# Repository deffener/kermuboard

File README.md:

== Kermuboard ==

- Normal/Stepped CAPS
- O-ring gasket mount
- Splitterino pepperino
- "Handwire" rotary encoder with huge clearance for >40mm knob
- Acrylic case

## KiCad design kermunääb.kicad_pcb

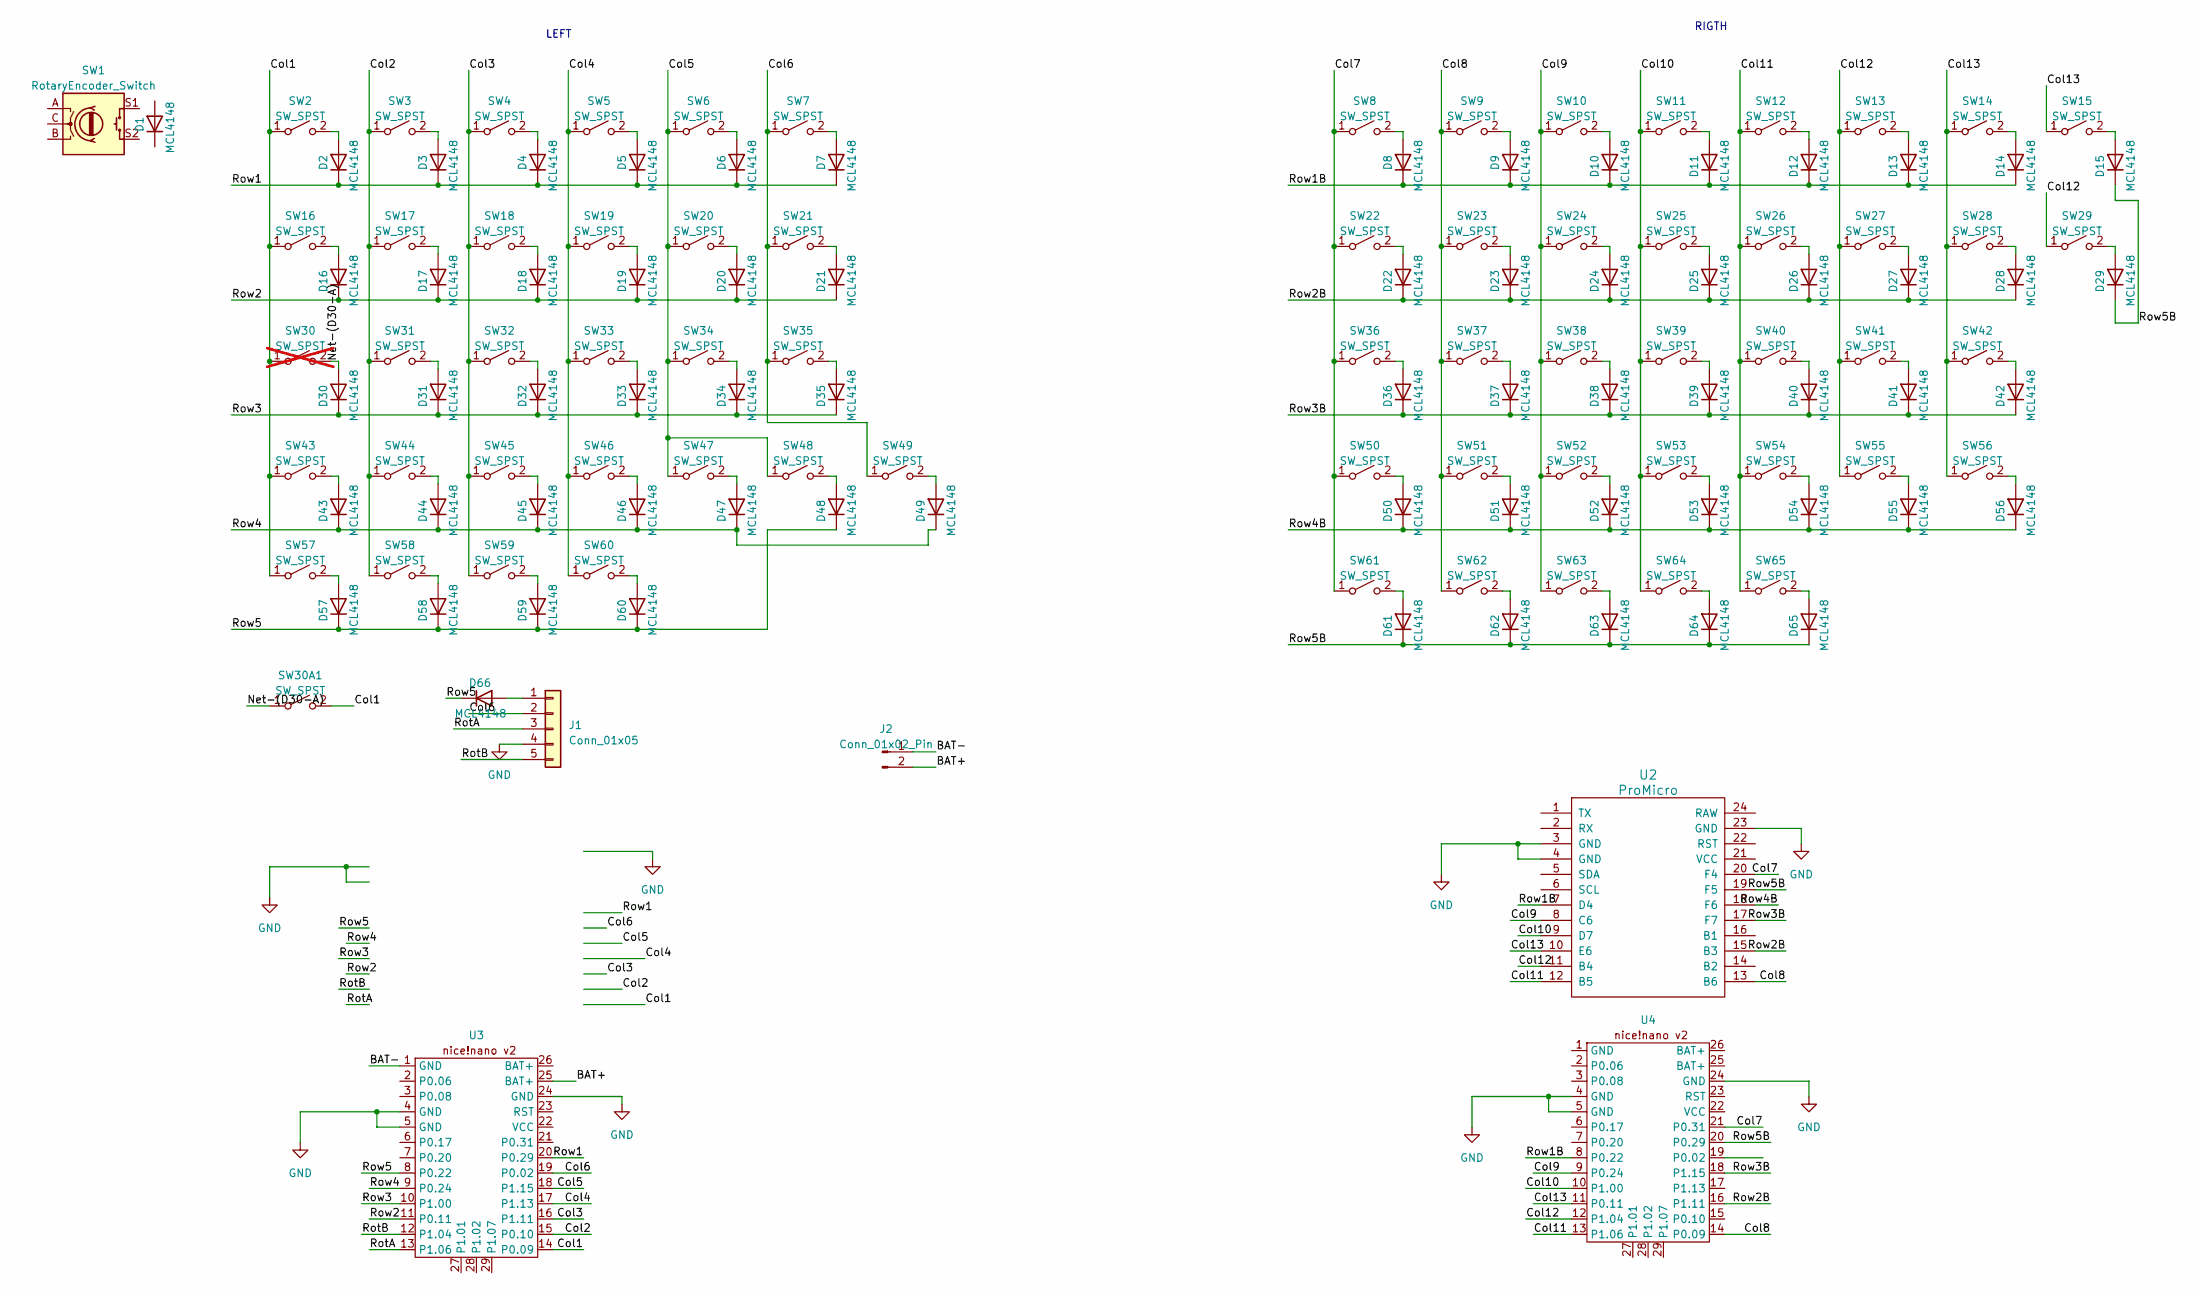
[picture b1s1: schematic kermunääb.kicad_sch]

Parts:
D1, D2, D3, D4, D5, D6, D7, D8, D9, D10, D11, D12, D13, D14, D15, D16, D17, D18, D19, D20, D21, D22, D23, D24, D25, D26, D27, D28, D29, D30, D31, D32, D33, D34, D35, D36, D37, D38, D39, D40, D41, D42, D43, D44, D45, D46, D47, D48, D49, D50, D51, D52, D53, D54, D55, D56, D57, D58, D59, D60, D61, D62, D63, D64, D65, D66: MCL4148; D_MicroMELF
J1: Conn_01x05; PinSocket_1x05_P2.54mm_Horizontal
J2: Conn_01x02_Pin; JST_XH_S2B-XH-A-1_1x02_P2.50mm_Horizontal
SW1: RotaryEncoder_Switch; RotaryEncoder_Alps_EC11E-Switch_Vertical_H20mm
SW2, SW3, SW4, SW5, SW6, SW7, SW8, SW9, SW10, SW11, SW12, SW13, SW14, SW17, SW18, SW19, SW20, SW21, SW22, SW23, SW24, SW25, SW26, SW27, SW28, SW31, SW32, SW33, SW34, SW35, SW36, SW37, SW38, SW39, SW40, SW41, SW42, SW44, SW45, SW46, SW47, SW48, SW49, SW50, SW51, SW52, SW53, SW54, SW55, SW58: SW_SPST; SW_Cherry_MX_PCB_1.00u
SW15: SW_SPST; SW_Cherry_MX_PCB_2.00u
SW16, SW57, SW59: SW_SPST; SW_Cherry_MX_PCB_1.50u
SW29: SW_SPST; SW_Cherry_MX_PCB_ISOEnter
SW30: SW_SPST; SW_Cherry_MX_PCB_1.75u; not fitted
SW30A1: SW_SPST; SW_Cherry_MX_PCB
SW43, SW62, SW63, SW64, SW65: SW_SPST; SW_Cherry_MX_PCB_1.25u
SW56, SW60, SW61: SW_SPST; SW_Cherry_MX_PCB_1.75u
U2: ProMicro
U3, U4: nice_nanov2_noextras

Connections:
/BAT+: J2.2, U3.25 (BAT+)
/BAT-: J2.1, U3.1 (GND)
/Col1: SW2.1 (A), SW16.1 (A), SW30.1 (A), SW30A1.2 (B), SW43.1 (A), SW57.1 (A), U3.14 (P0.09)
/Col2: SW3.1 (A), SW17.1 (A), SW31.1 (A), SW44.1 (A), SW58.1 (A), U3.15 (P0.10)
/Col3: SW4.1 (A), SW18.1 (A), SW32.1 (A), SW45.1 (A), SW59.1 (A), U3.16 (P1.11)
/Col4: SW5.1 (A), SW19.1 (A), SW33.1 (A), SW46.1 (A), SW60.1 (A), U3.17 (P1.13)
/Col5: SW6.1 (A), SW20.1 (A), SW34.1 (A), SW47.1 (A), SW48.1 (A), U3.18 (P1.15)
/Col6: J1.2, SW7.1 (A), SW21.1 (A), SW35.1 (A), SW49.1 (A), U3.19 (P0.02)
/Col7: SW8.1 (A), SW22.1 (A), SW36.1 (A), SW50.1 (A), SW61.1 (A), U2.20 (F4), U4.21 (P0.31)
/Col8: SW9.1 (A), SW23.1 (A), SW37.1 (A), SW51.1 (A), SW62.1 (A), U2.13 (B6), U4.14 (P0.09)
/Col9: SW10.1 (A), SW24.1 (A), SW38.1 (A), SW52.1 (A), SW63.1 (A), U2.8 (C6), U4.9 (P0.24)
/Col10: SW11.1 (A), SW25.1 (A), SW39.1 (A), SW53.1 (A), SW64.1 (A), U2.9 (D7), U4.10 (P1.00)
/Col11: SW12.1 (A), SW26.1 (A), SW40.1 (A), SW54.1 (A), SW65.1 (A), U2.12 (B5), U4.13 (P1.06)
/Col12: SW13.1 (A), SW27.1 (A), SW29.1 (A), SW41.1 (A), SW55.1 (A), U2.11 (B4), U4.12 (P1.04)
/Col13: SW14.1 (A), SW15.1 (A), SW28.1 (A), SW42.1 (A), SW56.1 (A), U2.10 (E6), U4.11 (P0.11)
/Net-(D30-A): D30.2 (A), SW30.2 (B), SW30A1.1 (A)
/RotA: J1.3, U3.13 (P1.06)
/RotB: J1.5, U3.12 (P1.04)
/Row1: D2.1 (K), D3.1 (K), D4.1 (K), D5.1 (K), D6.1 (K), D7.1 (K), U3.20 (P0.29)
/Row1B: D8.1 (K), D9.1 (K), D10.1 (K), D11.1 (K), D12.1 (K), D13.1 (K), D14.1 (K), U2.7 (D4), U4.8 (P0.22)
/Row2: D16.1 (K), D17.1 (K), D18.1 (K), D19.1 (K), D20.1 (K), D21.1 (K), U3.11 (P0.11)
/Row2B: D22.1 (K), D23.1 (K), D24.1 (K), D25.1 (K), D26.1 (K), D27.1 (K), D28.1 (K), U2.15 (B3), U4.16 (P1.11)
/Row3: D30.1 (K), D31.1 (K), D32.1 (K), D33.1 (K), D34.1 (K), D35.1 (K), U3.10 (P1.00)
/Row3B: D36.1 (K), D37.1 (K), D38.1 (K), D39.1 (K), D40.1 (K), D41.1 (K), D42.1 (K), U2.17 (F7), U4.18 (P1.15)
/Row4: D43.1 (K), D44.1 (K), D45.1 (K), D46.1 (K), D47.1 (K), D49.1 (K), U3.9 (P0.24)
/Row4B: D50.1 (K), D51.1 (K), D52.1 (K), D53.1 (K), D54.1 (K), D55.1 (K), D56.1 (K), U2.18 (F6)
/Row5: D48.1 (K), D57.1 (K), D58.1 (K), D59.1 (K), D60.1 (K), D66.1 (K), U3.8 (P0.22)
/Row5B: D15.1 (K), D29.1 (K), D61.1 (K), D62.1 (K), D63.1 (K), D64.1 (K), D65.1 (K), U2.19 (F5), U4.20 (P0.29)
GND: J1.4, U2.3 (GND), U2.4 (GND), U2.23 (GND), U3.4 (GND), U3.5 (GND), U3.24 (GND), U4.4 (GND), U4.5 (GND), U4.24 (GND)
unnamed: D2.2 (A), SW2.2 (B)
unnamed: D3.2 (A), SW3.2 (B)
unnamed: D4.2 (A), SW4.2 (B)
unnamed: D5.2 (A), SW5.2 (B)
unnamed: D6.2 (A), SW6.2 (B)
unnamed: D7.2 (A), SW7.2 (B)
unnamed: D8.2 (A), SW8.2 (B)
unnamed: D9.2 (A), SW9.2 (B)
unnamed: D10.2 (A), SW10.2 (B)
unnamed: D11.2 (A), SW11.2 (B)
unnamed: D12.2 (A), SW12.2 (B)
unnamed: D13.2 (A), SW13.2 (B)
unnamed: D14.2 (A), SW14.2 (B)
unnamed: D15.2 (A), SW15.2 (B)
unnamed: D16.2 (A), SW16.2 (B)
unnamed: D17.2 (A), SW17.2 (B)
unnamed: D18.2 (A), SW18.2 (B)
unnamed: D19.2 (A), SW19.2 (B)
unnamed: D20.2 (A), SW20.2 (B)
unnamed: D21.2 (A), SW21.2 (B)
unnamed: D22.2 (A), SW22.2 (B)
unnamed: D23.2 (A), SW23.2 (B)
unnamed: D24.2 (A), SW24.2 (B)
unnamed: D25.2 (A), SW25.2 (B)
unnamed: D26.2 (A), SW26.2 (B)
unnamed: D27.2 (A), SW27.2 (B)
unnamed: D28.2 (A), SW28.2 (B)
unnamed: D29.2 (A), SW29.2 (B)
unnamed: D31.2 (A), SW31.2 (B)
unnamed: D32.2 (A), SW32.2 (B)
unnamed: D33.2 (A), SW33.2 (B)
unnamed: D34.2 (A), SW34.2 (B)
unnamed: D35.2 (A), SW35.2 (B)
unnamed: D36.2 (A), SW36.2 (B)
unnamed: D37.2 (A), SW37.2 (B)
unnamed: D38.2 (A), SW38.2 (B)
unnamed: D39.2 (A), SW39.2 (B)
unnamed: D40.2 (A), SW40.2 (B)
unnamed: D41.2 (A), SW41.2 (B)
unnamed: D42.2 (A), SW42.2 (B)
unnamed: D43.2 (A), SW43.2 (B)
unnamed: D44.2 (A), SW44.2 (B)
unnamed: D45.2 (A), SW45.2 (B)
unnamed: D46.2 (A), SW46.2 (B)
unnamed: D47.2 (A), SW47.2 (B)
unnamed: D48.2 (A), SW48.2 (B)
unnamed: D49.2 (A), SW49.2 (B)
unnamed: D50.2 (A), SW50.2 (B)
unnamed: D51.2 (A), SW51.2 (B)
unnamed: D52.2 (A), SW52.2 (B)
unnamed: D53.2 (A), SW53.2 (B)
unnamed: D54.2 (A), SW54.2 (B)
unnamed: D55.2 (A), SW55.2 (B)
unnamed: D56.2 (A), SW56.2 (B)
unnamed: D57.2 (A), SW57.2 (B)
unnamed: D58.2 (A), SW58.2 (B)
unnamed: D59.2 (A), SW59.2 (B)
unnamed: D60.2 (A), SW60.2 (B)
unnamed: D61.2 (A), SW61.2 (B)
unnamed: D62.2 (A), SW62.2 (B)
unnamed: D63.2 (A), SW63.2 (B)
unnamed: D64.2 (A), SW64.2 (B)
unnamed: D65.2 (A), SW65.2 (B)
unnamed: D66.2 (A), J1.1

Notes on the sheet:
RIGTH
LEFT

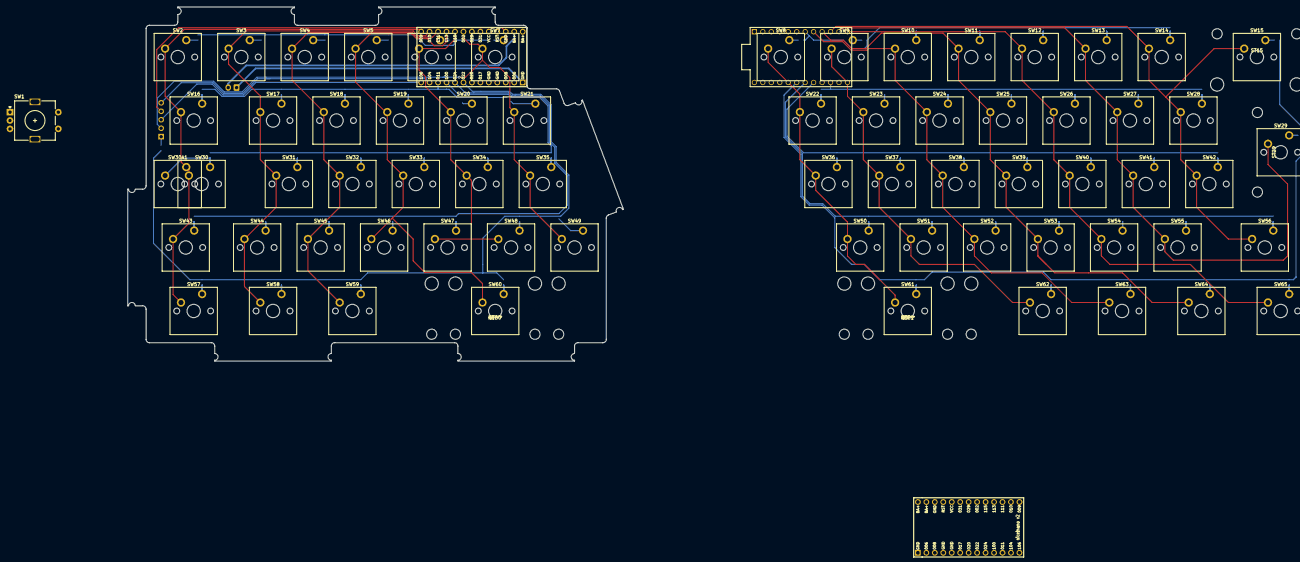
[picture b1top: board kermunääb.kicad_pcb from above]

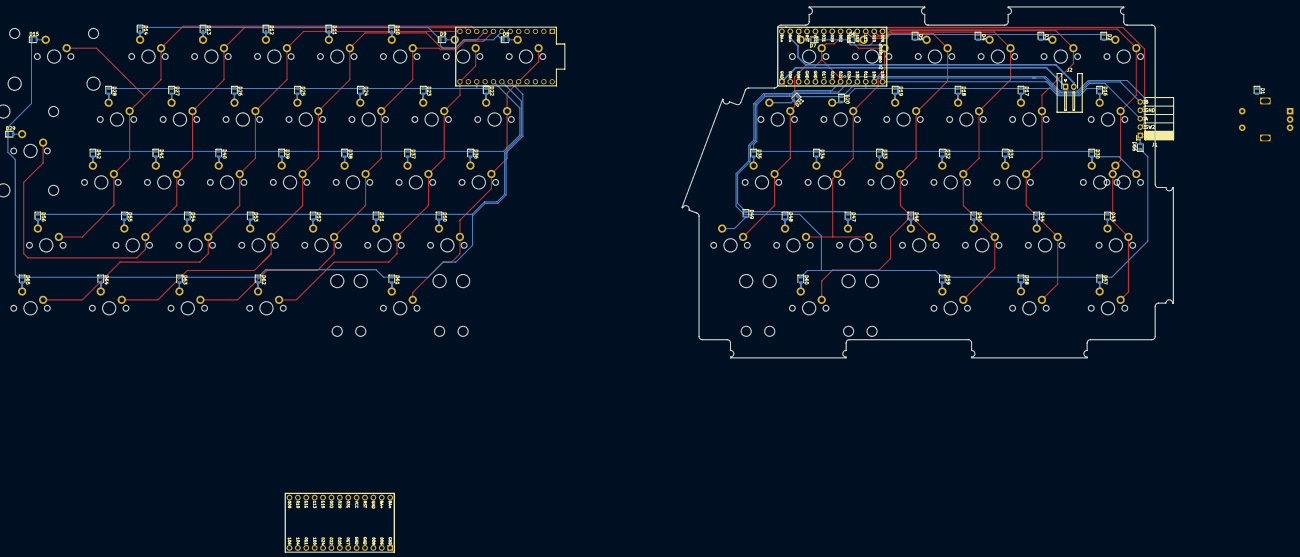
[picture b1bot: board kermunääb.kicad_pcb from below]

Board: 2 copper layers, 148.8 x 106.3 mm, 141 parts (70 on the bottom side), 93 nets.

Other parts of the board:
ST15, ST29: Stabilizer_Cherry_MX_2.00u
ST60, ST61: Stabilizer_Cherry_MX_3.00u

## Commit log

2024-02-28 First commit; Left side rev0, right side not routed
2024-02-28 change footprint for rotary header & add silk
2024-02-29 initial routing for right half and tweaks
2024-02-29 add initial edgecuts for left
2024-02-29 fix rotary encoder position & finetune left edgeCuts
2024-02-29 small changes
2024-03-27 changed left side to nicenano .gitignore and added battery wiring, still quite WIP
